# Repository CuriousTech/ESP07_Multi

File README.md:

# ESP07_Multi  Experiment board.  Multi-use  

I2C OLED and DHT-22 (back if regulator stays cool, otherwise extended facing top)  

BOM will have a few voltage regulator options chosen by voltage range, drop out, quiescent and support component cross compatibility.  The OLED can tax the 300mA regulator.

ADC option: Photocell or source voltage read  
IO0 could have been used for something (well, next time)  
IO12 option: button or PNP sink  
IO13 option: LED or PNP (or both)  
IO14 only raw I/O pad  
IO16 option: deepSleep, raw I/O or button.  (Note: IO16 has no internal pullup for button)

iot.php - simple script for saving data from a device.  
Create a directoy named "iot" in the same directory as iot.php  
A POST to this will create an XML formatted file using 'name' as the filename.xml  
All fields will be written as XML values overwriting the older file, and appended to filename.txt as JS array data.  
A GET /iot.php?name=file will return the data in the xml file.

chart.php?name=filename will draw a chart.  This one is designed for date, temp, rh, volts.

fwdip.php?name=myDevice&port=number will create server/iot/myDevice.php with script to forward all GET data to IP of device that created it.  The global IP and current date/time are also returned to the creator.

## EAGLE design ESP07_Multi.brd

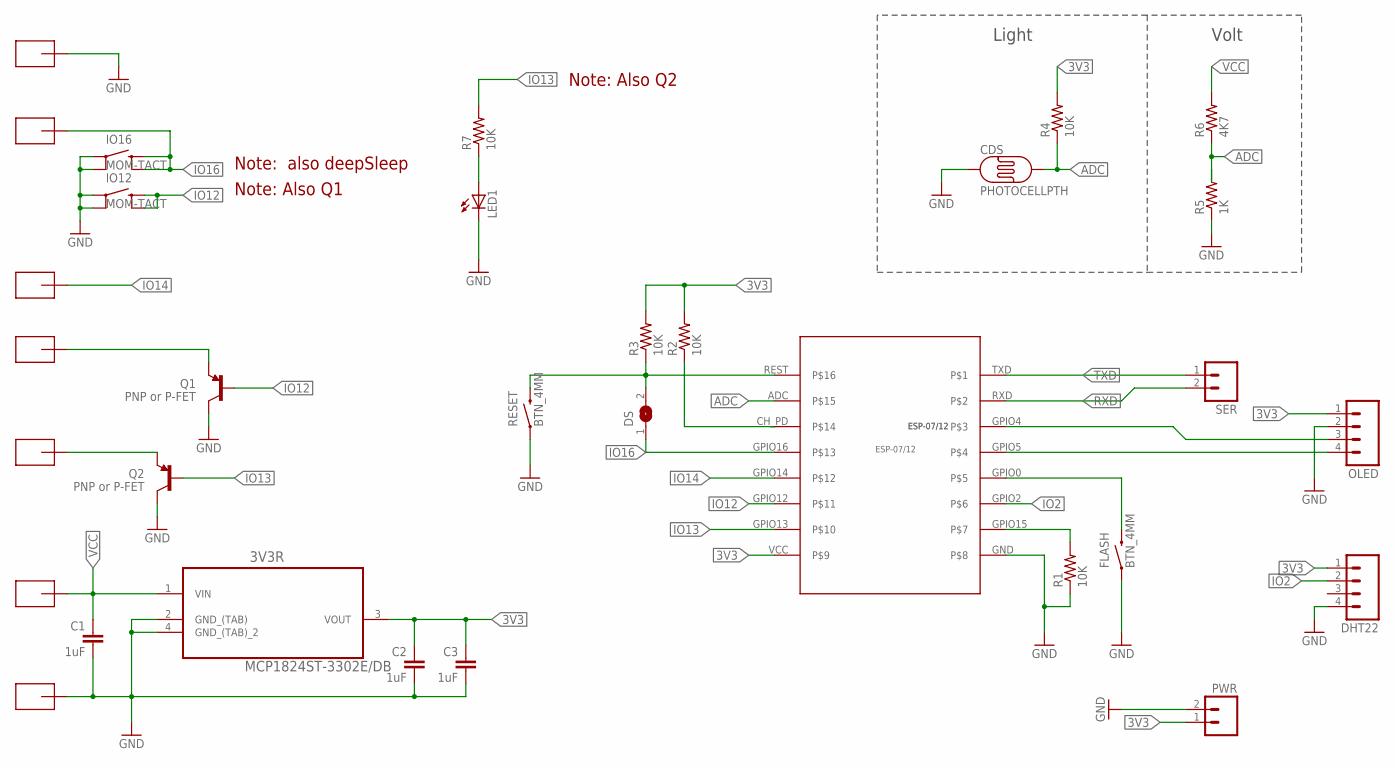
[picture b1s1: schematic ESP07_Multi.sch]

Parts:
3V3R: MCP1824ST-3302E/DB; SOT230P700X180-4N
C1, C2, C3: 1uF; 0805-CAP
CDS: PHOTOCELLPTH; PHOTOCELL
DHT22: M04PTH; 1X04
DS: SJ
FLASH: BTN_4MM
IO12, IO16: MOM-TACT; TACTILE-SMD
LED1: LEDCHIPLED_0805; CHIPLED_0805
OLED: M04PTH; 1X04
PWR: M02PTH; 1X02
Q1, Q2: PNP or P-FET; SOT23-3
R1, R2, R3, R4, R7: 10K; 0805
R5: 1K; 0805
R6: 4K7; 0805
RESET: BTN_4MM
SER: M02PTH; 1X02
U$1: ESP-07/12
U$2, U$3, U$4, U$5, U$6, U$7, U$8: SMD-PAD-SM; SMD-PAD3

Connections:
3V3: 3V3R.3 (VOUT), C2.1, C3.1, DHT22.1, OLED.1, PWR.1, R2.2, R3.2, R4.2, U$1.VCC
ADC: CDS.2, R4.1, R5.2, R6.1, U$1.ADC
GND: 3V3R.2 (GND_(TAB)), 3V3R.4 (GND_(TAB)_2), C1.2, C2.2, C3.2, CDS.1, DHT22.4, FLASH.1, IO12.1, IO12.2 (3), IO16.1, IO16.2 (3), LED1.C, OLED.2, PWR.2, Q1.3 (C), Q2.3 (C), R1.1, R5.1, RESET.1, U$1.GND, U$2.P$1, U$5.P$1
IO2: DHT22.2, U$1.GPIO2
IO12: IO12.3 (2), IO12.4, Q1.1 (B), U$1.GPIO12
IO13: Q2.1 (B), R7.2, U$1.GPIO13
IO14: U$1.GPIO14, U$4.P$1
IO16: DS.1, IO16.3 (2), IO16.4, U$1.GPIO16, U$6.P$1
unnamed: LED1.A, R7.1
unnamed: OLED.3, U$1.GPIO4
unnamed: Q2.2 (E), U$8.P$1
unnamed: Q1.2 (E), U$7.P$1
unnamed: R1.2, U$1.GPIO15
unnamed: OLED.4, U$1.GPIO5
unnamed: FLASH.2, U$1.GPIO0
unnamed: R2.1, U$1.CH_PD
unnamed: DS.2, R3.1, RESET.2, U$1.REST
RXD: SER.2, U$1.RXD
TXD: SER.1, U$1.TXD
VCC: 3V3R.1 (VIN), C1.1, R6.2, U$3.P$1

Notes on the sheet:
Volt
Light
Note: also deepSleep
Note: Also Q1
Note: Also Q2

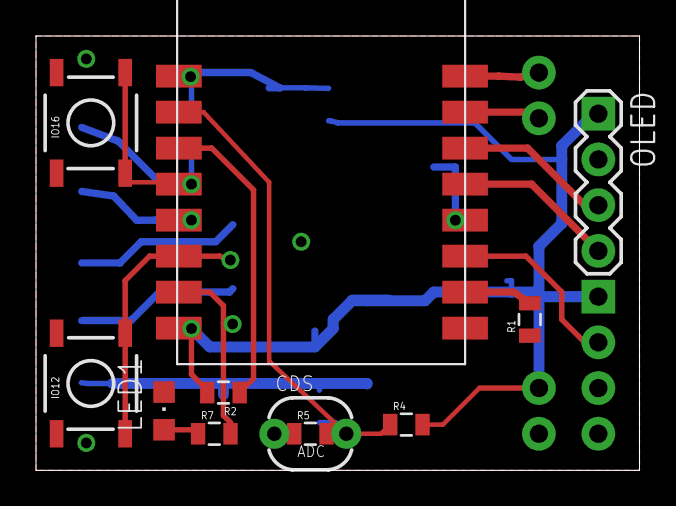
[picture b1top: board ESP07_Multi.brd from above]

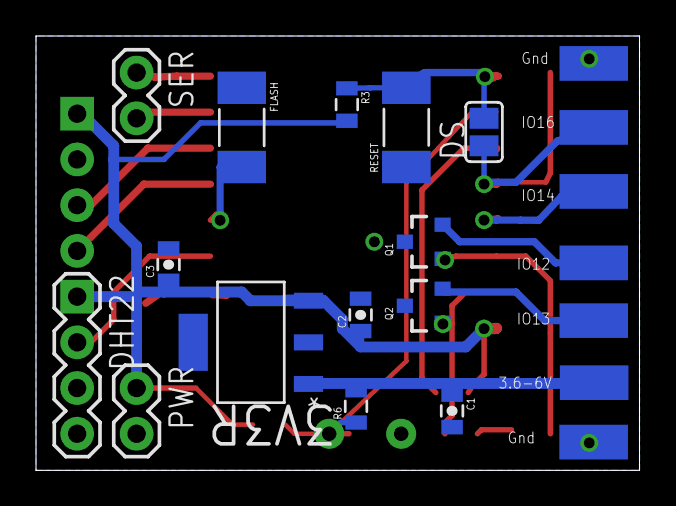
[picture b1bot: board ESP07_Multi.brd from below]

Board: 2 copper layers, 33.5 x 24.1 mm, 32 parts (21 on the bottom side), 20 nets.

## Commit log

2015-08-13 Added popup
2015-10-08 Added a current time echo

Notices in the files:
parts and their libraries:
SparkFun-Connectors: Licensing: Creative Commons ShareAlike 4.0 International - https://creativecommons.org/licenses/by-sa/4.0
